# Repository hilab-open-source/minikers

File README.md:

# MiniKers: Interaction-Powered Smart Environment Automation

## About
MiniKers is a fleet of interaction-powered environment automation devices that harnesses energy from user interactions, achieving self-sustaining automatic operations that could last for long periods of time without human intervention (e.g., exchanging batteries). MiniKers system opens opportunities for turning user interactions into power sources for research in ubiquitous computing, IoT, and cyber-physical systems.

Please refer to the [paper](https://dl.acm.org/doi/10.1145/3550287) for more details.

## Hardware
We designed a circuit to accomodate the manual and automatic operations of everyday objects. The circuit features a discharging and a charging mode to support the motor being used as either an actuator or a generator. It has a rechargeable supercapacitor and a Lithium-ion Polymer (Li-Po) battery. 

## Contact
[info@hilab.dev](https://mail.google.com/mail/u/0/?fs=1&tf=cm&source=mailto&to=info@hilab.dev)

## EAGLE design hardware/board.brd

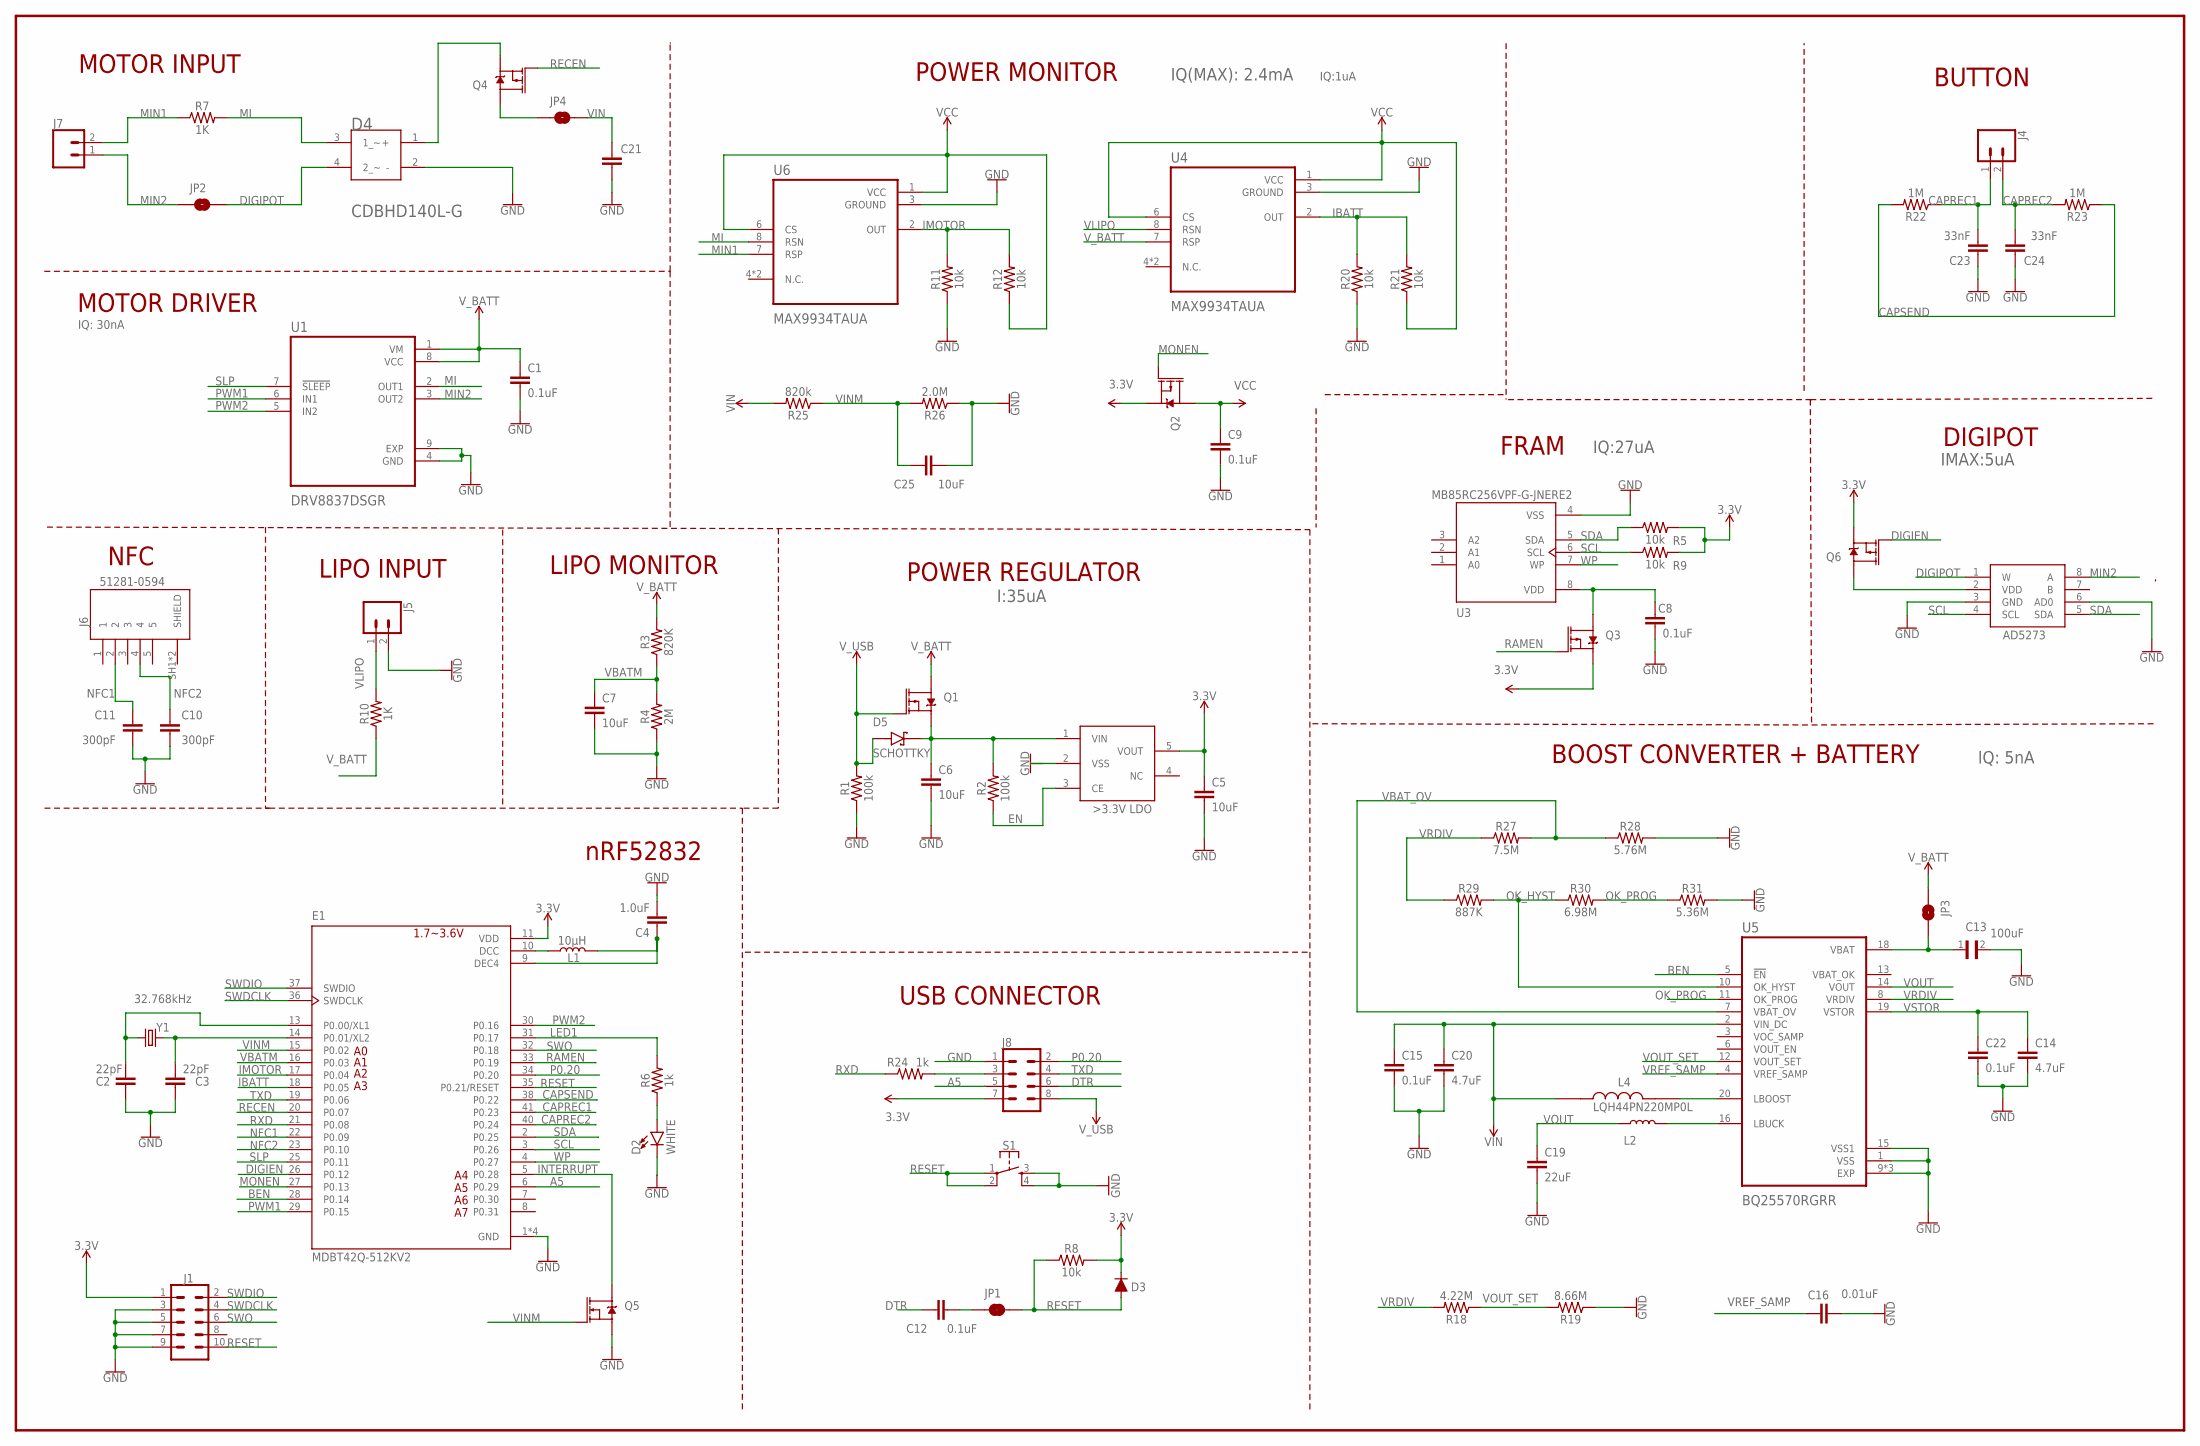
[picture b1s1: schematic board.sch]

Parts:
C1, C8, C9, C12, C15, C22: 0.1uF; 0603
C2, C3: 22pF; 0603
C4: 1.0uF; 0603
C5, C6, C7, C25: 10uF; 0603
C10, C11: 300pF; 0603
C13: 100uF; CAPC4532X127N
C14, C20: 4.7uF; 0805
C16: 0.01uF; 0603
C19: 22uF; 0603
C21: 2.2uF; 0805
C23, C24: 33nF; 0603
D2: WHITE; LED-0603
D3: 250mA/100V; SOD-323
D4: COMCHIP_CDBHD140L-GCOMCHIP_CDBHD140L-G_0_0; COMCHIP_CDBHD140L-G_0
D5: SCHOTTKY; SOD3715X145N
E1: MDBT42Q-512KV2; RAYTAC_MDBT42Q-512KV2
J1: CONN_05X2SHD_SMD; 2X5-SHROUDED_SMD
J4, J5, J7: CONN_02; 1X02
J6: 51281-0594; MOLEX_51281-0594
J8: CONN_04X2; 2X4
JP1: JUMPER-SMT_2_NC_TRACE_SILK; SMT-JUMPER_2_NC_TRACE_SILK
JP2, JP3, JP4: JUMPER-SMT_2_NO_SILK; SMT-JUMPER_2_NO_SILK
L1: 10µH; 0805
L2: 3.3µH/±20%/450mA; 0805
L4: LQH44PN220MP0L; IND_LQH44PN220MP0L
Q1: MOSFET_PCH-DMG2307L; SOT23-3
Q2, Q3, Q4, Q6: 2.5A/30V/105mΩ; SOT23-3
Q5: 5.8A/30V/35mΩ; SOT23-3
R1, R2: 100k; 0603
R3: 820K; 0603
R4: 2M; 0603
R5, R8, R9, R11, R12, R20, R21: 10k; 0603
R6, R24: 1k; 0603
R7, R10: 1K; 0603
R18: 4.22M; 0603
R19: 8.66M; 0603
R22, R23: 1M; 0603
R25: 820k; 0603
R26: 2.0M; 0603
R27: 7.5M; 0603
R28: 5.76M; 0603
R29: 887K; 0603
R30: 6.98M; 0603
R31: 5.36M; 0603
S1: MOMENTARY-SWITCH-SPST-2-SMD-4.6X2.8MM; TACTILE_SWITCH_SMD_4.6X2.8MM
U1: DRV8837DSGR; SON50P200X200X80-9N
U3: MB85RC256VPF-G-JNERE2; SOP127P797X210-8N
U4, U6: MAX9934TAUA; SOP65P490X110-8N
U5: BQ25570RGRR; QFN50P350X350X100-21N
U$1: IC_X8107AC20MR-GSMD; IC_XC8107AC20MR-G
U$2: AD5273; SOT65P280X145-8N
Y1: 32.768kHz; CRYSTAL-SMD-3.2X1.5MM

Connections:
BEN: E1.28 (P0.14), U5.5 (!EN)
CAPREC1: C23.2, E1.41 (P0.23), J4.1, R22.1
CAPREC2: C24.2, E1.40 (P0.24), J4.2, R23.2
CAPSEND: E1.38 (P0.22), R22.2, R23.1
DIGIEN: E1.26 (P0.12), Q6.1 (G)
DIGIPOT: D4.4 (2_~), JP2.2, U$2.1 (W)
DTR: C12.1, J8.6
EN: R2.1, U$1.3 (CE)
GND: C1.2, C2.1, C3.1, C4.2, C5.2, C6.2, C7.2, C8.2, C9.2, C10.2, C11.2, C13.2, C14.2, C15.2, C16.2, C19.2, C20.2, C21.2, C22.2, C23.1, C24.1, C25.2, D2.C, D4.2 (-), E1.1 (GND), E1.12 (GND), E1.24 (GND), E1.39 (GND), J1.3, J1.5, J1.7, J1.9, J5.2, J8.1, Q5.2 (S), R1.1, R4.1, R11.1, R19.1, R20.1, R26.1, R28.2, R31.2, S1.3, S1.4, U1.4 (GND), U1.9 (EXP), U3.4 (VSS), U4.3 (GROUND), U5.1 (VSS), U5.9 (EXP), U5.15 (VSS1), U5.17 (EXP), U5.21 (EXP), U6.3 (GROUND), U$1.2 (VSS), U$2.3 (GND), U$2.6 (AD0)
IBATT: E1.18 (P0.05), R20.2, R21.2, U4.2 (OUT)
IMOTOR: E1.17 (P0.04), R11.2, R12.2, U6.2 (OUT)
INTERRUPT: E1.5 (P0.28), Q5.3 (D)
LED1: E1.31 (P0.17), R6.2
MI: D4.3 (1_~), R7.2, U1.2 (OUT1), U6.8 (RSN)
MIN1: J7.2, R7.1, U6.7 (RSP)
MIN2: J7.1, JP2.1, U1.3 (OUT2), U$2.8 (A)
MONEN: E1.27 (P0.13), Q2.1 (G)
unnamed: E1.10 (DCC), L1.1
unnamed: L4.2, U5.20 (LBOOST)
unnamed: C3.2, E1.14 (P0.01/XL2), Y1.P$2 (2)
unnamed: C4.1, E1.9 (DEC4), L1.2
unnamed: L2.2, U5.16 (LBUCK)
unnamed: C12.2, JP1.1
unnamed: C6.1, D5.C (K), Q1.2 (S), R2.2, U$1.1 (VIN)
unnamed: Q6.3 (D), U$2.2 (VDD)
unnamed: C13.1, JP3.2, U5.18 (VBAT)
unnamed: C2.2, E1.13 (P0.00/XL1), Y1.P$1 (1)
unnamed: JP4.1, Q4.3 (D)
unnamed: D2.A, R6.1
unnamed: J8.3, R24.2
NFC1: C11.1, E1.22 (P0.09), J6.2
NFC2: C10.1, E1.23 (P0.10), J6.4
OK_HYST: R29.2, R30.1, U5.10 (OK_HYST)
OK_PROG: R30.2, R31.1, U5.11 (OK_PROG)
P0.20: E1.34 (P0.20), J8.2
PWM1: E1.29 (P0.15), U1.6 (IN1)
PWM2: E1.30 (P0.16), U1.5 (IN2)
RAMEN: E1.33 (P0.19), Q3.1 (G)
RECEN: E1.20 (P0.07), Q4.1 (G)
RESET: D3.A, E1.35 (P0.21/RESET), J1.10, JP1.2, R8.1, S1.1, S1.2
RXD: E1.21 (P0.08), R24.1
SCL: E1.3 (P0.26), R9.1, U3.6 (SCL), U$2.4 (SCL)
SDA: E1.2 (P0.25), R5.1, U3.5 (SDA), U$2.5 (SDA)
SLP: E1.25 (P0.11), U1.7 (!SLEEP)
SWDCLK: E1.36 (SWDCLK), J1.4
SWDIO: E1.37 (SWDIO), J1.2
SWO: E1.32 (P0.18), J1.6
TXD: E1.19 (P0.06), J8.4
VBATM: C7.1, E1.16 (P0.03), R3.1, R4.2
VBAT_OV: R27.2, R28.1, U5.7 (VBAT_OV)
VCC: C9.1, Q2.3 (D), R12.1, R21.1, U4.1 (VCC), U4.6 (CS), U6.1 (VCC), U6.6 (CS)
VIN: C15.1, C20.1, C21.1, JP4.2, L4.1, R25.2, U5.2 (VIN_DC)
VINM: C25.1, E1.15 (P0.02), Q5.1 (G), R25.1, R26.2
VLIPO: J5.1, R10.2, U4.8 (RSN)
VOUT: C19.1, L2.1, U5.14 (VOUT)
VOUT_SET: R18.1, R19.2, U5.12 (VOUT_SET)
VRDIV: R18.2, R27.1, R29.1, U5.8 (VRDIV)
VREF_SAMP: C16.1, U5.4 (VREF_SAMP)
VSTOR: C14.1, C22.1, U5.19 (VSTOR)
V_BATT: C1.1, JP3.1, Q1.3 (D), R3.2, R10.1, U1.1 (VM), U1.8 (VCC), U4.7 (RSP)
V_USB: D5.A, J8.8, Q1.1 (G), R1.2
WP: E1.4 (P0.27), U3.7 (WP)

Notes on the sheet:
LIPO INPUT
nRF52832
LIPO MONITOR
POWER REGULATOR
USB CONNECTOR
MOTOR INPUT
MOTOR DRIVER
POWER MONITOR
BOOST CONVERTER + BATTERY
FRAM
DIGIPOT
1.7~3.6V
IQ:27uA
IQ: 5nA
IQ: 30nA
IMAX:5uA
IQ(MAX): 2.4mA
IQ:1uA
I:35uA
BUTTON
NFC

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
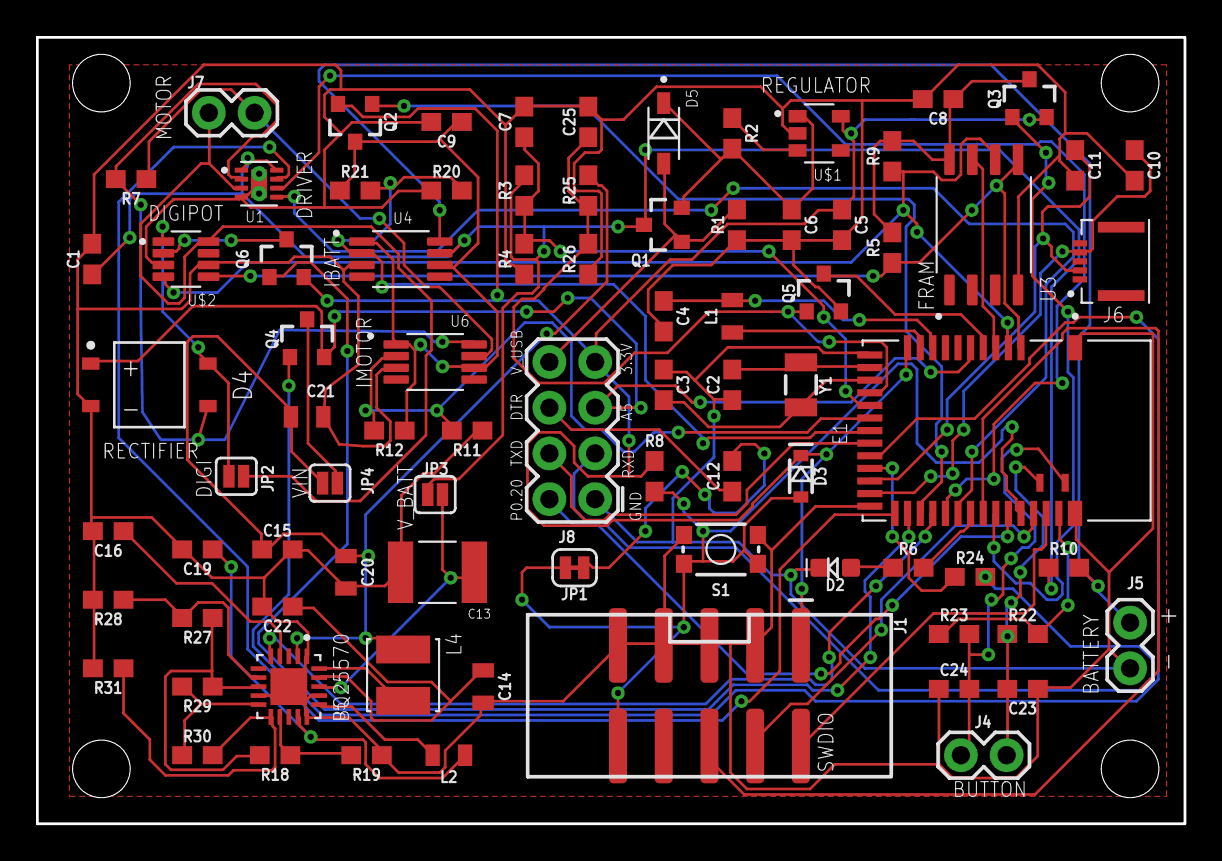
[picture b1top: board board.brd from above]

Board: 2 copper layers, 63.8 x 43.7 mm, 82 parts (0 on the bottom side), 65 nets.

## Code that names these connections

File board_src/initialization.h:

#ifndef _INITISLIZAION_H_
#define _INITISLIZAION_H_

#include "energy_control.h"

#define PIN_UMOTOR A0
#define PIN_UBAT A1
#define PIN_IMOTOR A2
#define PIN_IBAT A3

#define LED 17
#define RECEN 7
#define BEN 14
#define MONEN 13
#define RAMEN 19
#define DIGIEN 12
#define BUT 23

#define SLP 11
#define PWM1 15
#define PWM2 16

#define WAKE_LOW_PIN  PIN_A4
//#define WAKE_HIGH_PIN PIN_A5

#define INTERRUPT_PIN  PIN_A5

#define SDA 25
#define SCL 26

void DATA_LOGGING();
void PIN_SETUP();
void manual_input_callback();


#endif

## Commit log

2022-09-09 ⚙️ Mechanisms
2022-09-09 Add hardware files
2022-09-09 Add board src
2022-09-09 Add images
2022-09-10 .DS_Store removed
2022-09-10 Add files
2022-09-10 Add board images
2022-09-10 Change files
2022-09-10 🌠 Images
2022-09-10 💻 Source code
2022-09-10 👩‍🏭 PCB files
2022-09-10 🧑‍💻 Source code
2022-09-17 Add app files
2022-09-19 Update app to use firebase + misc cleanup

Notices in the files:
parts and their libraries:
SparkFun-Capacitors: Licensing: Creative Commons ShareAlike 4.0 International - https://creativecommons.org/licenses/by-sa/4.0
